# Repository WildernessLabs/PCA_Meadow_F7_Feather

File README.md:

# PCA_Meadow_F7_Micro
PCA (Printed Circuit Assembly) design for the F7 Micro development board.

## Drawings
* [Schematic](https://github.com/WildernessLabs/PCA_Meadow_F7_Micro/blob/main/Assembly/PCA_Meadow_F7_Micro_SCH_V2c.pdf)
* [Top Assembly](https://github.com/WildernessLabs/PCA_Meadow_F7_Micro/blob/main/Assembly/PCA_Meadow_F7_MicroV2c.pdf)
* [BOM](https://github.com/WildernessLabs/PCA_Meadow_F7_Micro/blob/main/Assembly/PCA_Meadow_F7_Micro_bom_V2c.xlsx)

## Pin Out
### Left Header

| F7 Pin Name | STM Pin Function Name | Alt Functions | Additional Functions |
|-------------|-------------|-------------------------|-----------|
| `A00` | `PA4` | SPI1_NSS/I2S1_WS, SPI3_NSS/I2S3_WS, USART2_CK, SPI6_NSS, OTG_HS_SOF, DCMI_HSYNC, LCD_VSYNC, EVENTOUT | ADC1_IN4, ADC2_IN4, DAC_OUT1 |
| `A01` | `PA5` | TIM2_CH1/TIM2_ETR, TIM8_CH1N, SPI1_SCK/I2S1_CK, SPI6_SCK, OTG_HS_ULPI_CK, LCD_R4, EVENTOUT | ADC1_IN5, ADC2_IN5, DAC_OUT2 |
| `A02` | `PA3` | TIM2_CH4, TIM5_CH4, TIM9_CH2, USART2_RX, LCD_B2, OTG_HS_ULPI_D0, ETH_MII_COL, LCD_B5, EVENTOUT | ADC1_IN3, ADC2_IN3, ADC3_IN |
| `A03` | `PB0` | TIM1_CH2N, TIM3_CH3, TIM8_CH2N, DFSDM_CKOUT, UART4_CTS, LCD_R3, OTG_HS_ULPI_D1, ETH_MII_RXD2, LCD_G1, EVENTOUT | ADC1_IN8, ADC2_IN8 |
| `A04` | `PB1` | TIM1_CH3N, TIM3_CH4, TIM8_CH3N, DFSDM_DATIN1, LCD_R6, OTG_HS_ULPI_D2, ETH_MII_RXD3, LCD_G0, EVENTOUT | ADC1_IN9, ADC2_IN9 |
| `A05` | `PC0` | DFSDM_CKIN0, DFSDM_DATIN4, SAI2_FS_B, OTG_HS_ULPI_STP, FMC_SDNWE, LCD_R5, EVENTOUT | ADC1_IN10, ADC2_IN10, ADC3_IN10 |
| `SPI3_SCK` | `PC10` | DFSDM_CKIN5, SPI3_SCK/I2S3_CK, USART3_TX, UART4_TX, QUADSPI_BK1_IO1, SDMMC1_D2, DCMI_D8, LCD_R2, EVENTOUT |
| `SPI3_COPI` | `PB5` | UART5_RX, TIM3_CH2, I2C1_SMBA, SPI1_MOSI/I2S1_SD, SPI3_MOSI/I2S3_SD, SPI6_MOSI, CAN2_RX, OTG_HS_ULPI_D7, ETH_PPS_OUT, FMC_SDCKE1, DCMI_D10, LCD_G7, EVENTOUT |
| `SPI3_CIPO` | `PC11` | DFSDM_DATIN5, SPI3_MISO, USART3_RX, UART4_RX, QUADSPI_BK2_NCS, SDMMC1_D3, DCMI_D4, EVENTOUT |
| `D00`/`COM4_RX` | `PI9` | UART4_RX, CAN1_RX, FMC_D30, LCD_VSYNC, EVENTOUT |
| `D01`/`COM4_TX` | `PH13` | TIM8_CH1N, UART4_TX, CAN1_TX, FMC_D21, LCD_G2, EVENTOUT |
| `D02` | `PH10` | TIM5_CH1, I2C4_SMBA, FMC_D18, DCMI_D1, LCD_R4, EVENTOUT |
| `D03`/`CAN_RX` | `PB8` | I2C4_SCL, TIM4_CH3, TIM10_CH1, I2C1_SCL, DFSDM_CKIN7, UART5_RX, CAN1_RX, SDMMC2_D4, ETH_MII_TXD3, SDMMC1_D4, DCMI_D6, LCD_B6, EVENTOUT |
| `D04`/`CAN_TX` | `PB9` | I2C4_SDA, TIM4_CH4, TIM11_CH1, I2C1_SDA, SPI2_NSS/I2S2_WS, DFSDM_DATIN7, UART5_TX, CAN1_TX, SDMMC2_D5, I2C4_SMBA, SDMMC1_D5, DCMI_D7, LCD_B7, EVENTOUT |

### Right Header

| F7 Pin Name | STM Pin Function Name | Alt Functions | Additional Functions |
|-------------|-------------|-------------------------|-----------|
| `D05` | `PB4` | NJTRST, TIM3_CH1, SPI1_MISO, SPI3_MISO, SPI2_NSS/I2S2_WS, SPI6_MISO, SDMMC2_D3, CAN3_TX, UART7_TX, EVENTOUT |
| `D06`/`I2S2_CK` | `PB13` | I2C2_SMBA, SPI5_SCK, TIM12_CH1, ETH_MII_RXD2, FMC_SDNE1, DCMI_D8, EVENTOUT |
| `D07`/`I2C_SDA` | `PB7` | TIM4_CH2, I2C1_SDA, DFSDM_CKIN5, USART1_RX, I2C4_SDA, FMC_NL, DCMI_VSYNC, EVENTOUT |
| `D08`/`I2C_SCK` | `PB6` | UART5_TX, TIM4_CH1, HDMI_CEC, I2C1_SCL, DFSDM_DATIN5, USART1_TX, CAN2_TX, QUADSPI_BK1_NCS, I2C4_SCL, FMC_SDNE1, DCMI_D5, EVENTOUT |
| `D09`/`I2S2_MCK`/`COM6_TX` | `PC6` | TIM3_CH1, TIM8_CH1, I2S2_MCK, DFSDM_CKIN3, USART6_TX, FMC_NWAIT, SDMMC2_D6, SDMMC1_D6, DCMI_D0, LCD_HSYNC, EVENTOUT |
| `D10`/`COM6_RX` | `PC7` | TIM3_CH2, TIM8_CH2, I2S3_MCK, DFSDM_DATIN3, USART6_RX, FMC_NE1, SDMMC2_D7, SDMMC1_D7, DCMI_D1, LCD_G6, EVENTOUT |
| `D11`/`I2S2_CKIN` | `PC9` | MCO2, TIM3_CH4, TIM8_CH4, I2C3_SDA, I2S_CKIN, UART5_CTS, QUADSPI_BK1_IO0, LCD_G3, SDMMC1_D1, DCMI_D3, LCD_B2, EVENTOUT |
| `D12`/`COM1_TX` | `PB14` | TIM1_CH2N, TIM8_CH2N, USART1_TX, SPI2_MISO, DFSDM_DATIN2, USART3_RTS, UART4_RTS, TIM12_CH1, SDMMC2_D0, OTG_HS_DM, EVENTOUT |
| `D13`/`COM1_RX`/`I2S2_SD` | `PB15` | RTC_REFIN, TIM1_CH3N, TIM8_CH3N, USART1_RX, SPI2_MOSI/I2S2_SD, DFSDM_CKIN2, UART4_CTS, TIM12_CH2, SDMMC2_D1, OTG_HS_DP, EVENTOUT |
| `D14`/`I2S2_WS` | `PB12` | TIM1_BKIN, I2C2_SMBA, SPI2_NSS/I2S2_WS, DFSDM_DATIN1, USART3_CK, UART5_RX, CAN2_RX, OTG_HS_ULPI_D5, ETH_MII_TXD0/ETH_RMII _TXD0, OTG_HS_ID, EVENTOUT |
| `D15` | `PG12` | LPTIM1_IN1, SPI6_MISO, SPDIF_RX1, USART6_RTS, LCD_B4, SDMMC2_D3, FMC_NE4, LCD_B1, EVENTOUT |

## Change Log

### Revision V2.D
* Move to Kicad 6.0.2
* 5V pin is now connected directly to 5V VBUS. Note: If you try to power directly from an external source and connect USB cable you can damage your USB port.
* More schematic clean up
* Change name to F7 Feather

### Revision V2.C1
* Documentaion Changes to Fab Drawing: 
  * do not modify pad sizes without permission from Wilderness Labs
  * fixed errors in stack up and other parts of the notes
* Cleaned up folders to remove all rev B files and zip up rev 2.C files
### Revison V2.C 
* Fixed issue with Batery and VBUS, 
### Revision V2.B
 * Added pogo test points for usb [Schematic and Layout]
 * Changed part number for flash (U2) [Schematic /BOM ]
 * Made pads for Buttons 10% smaller in each directions [Layout]
 * Matched the Trace width of the Quad SPI to the Flash chip [Layout]
 * LDO changed to have lower drop out voltage. 3.3V wasn't regulated when using the batter [Schematic/BOM, and Layout]
 * New LDO has an Enable input so removed the power FET that turned on/off the power to the LDO. Drop out now 0.35V should work 20 - 3.6V. anything above 7V will probably break the LDO under continuous load.
 * Changed pinout of the main headers [Schematic and Layout]

### Revision V2.A
 * Added castelations for JTAG and ESP32 UART
 * Upgrade flash to 512Mega Bit part
 * Changed the USB power switch to remove the discharge circuit.

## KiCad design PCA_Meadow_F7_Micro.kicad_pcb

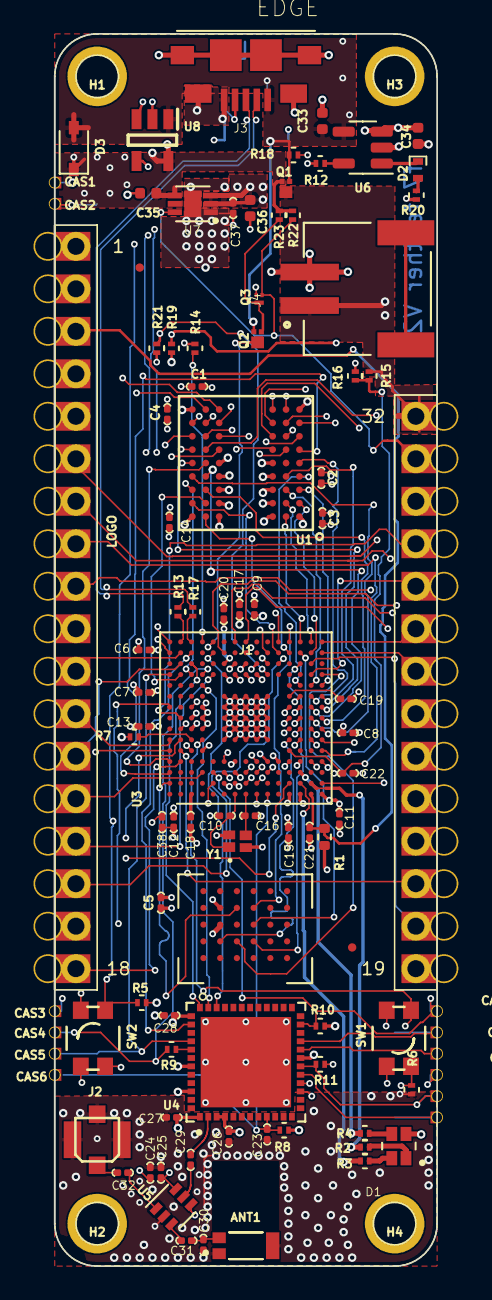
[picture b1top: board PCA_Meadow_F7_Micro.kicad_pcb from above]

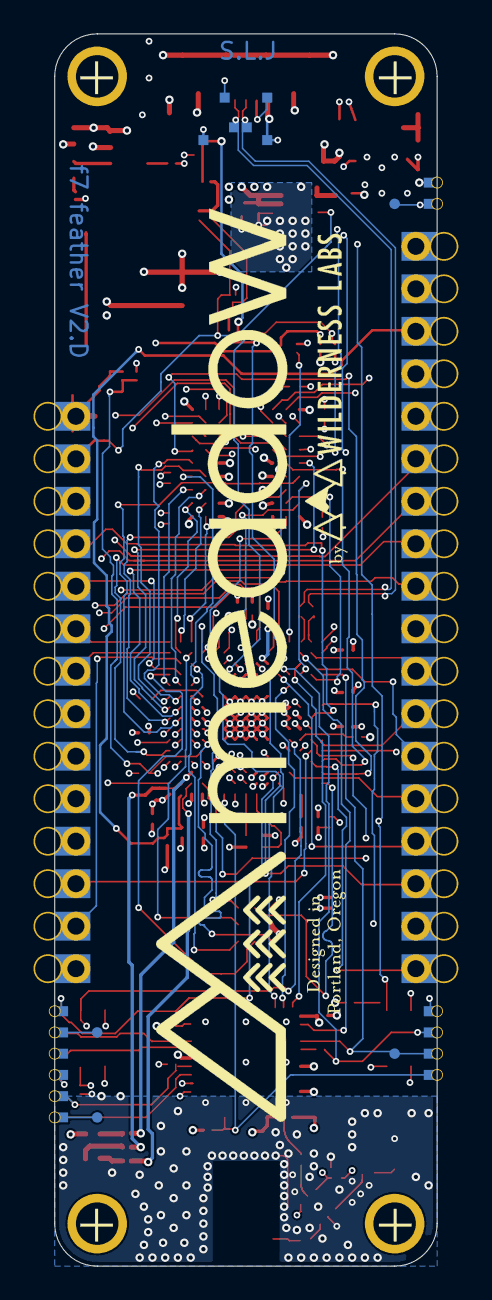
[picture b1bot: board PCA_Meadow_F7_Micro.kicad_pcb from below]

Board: 6 copper layers, 22.9 x 73.7 mm, 110 parts (10 on the bottom side), 128 nets.

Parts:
ANT1: W3008C; ANTENNA_W3008C
C1, C6, C7, C8, C9, C11, C12, C13, C14, C15, C17, C18, C21: C_0201_0.47UF_6.3V_X5R; C_0201
C2, C3, C4, C5, C22, C23, C24, C25, C37, C38: C_0201_0.1UF_10V_X5R; C_0201
C10, C16: C_0201_8pF_50V_C0G; C_0201
C19, C20: C_0201_2.2UF_10V_X5R; C_0201
C26, C27, C28: C_0201_4.7UF_6.3V_X5R; C_0201
C29, C31, C32: C_0201_100PF_50V_C0G; C_0201
C30: C_0201_1.8pF_50V_C0G; C_0201
C33, C34: C_0402_4.7UF_10V_X5R_10%; C_0402_1005Metric
C35, C36: C_0402_10UF_10V_X5R; C_0402_1005Metric
CAS1, CAS2, CAS3, CAS4, CAS5, CAS6, CAS7, CAS8, CAS9, CAS10, CAS11, CAS12: CAST_0.6X0.8MM; CAST_SQ_0.6X0.8MM
D1: LTST-C19HE1WT; LED_LTST-C19HE1WT
D2: LED_O_QBLP595-O; LED_0402
D3: BAT60A; D_SOD-323
H1, H2, H3, H4: MTGP356H254
J1: MEADOWF7MICRO_WITH_CAST_OUTLINE; MeadowF7Micro_w_cast
J2: A-1JB; AMPHENOL_A-1JB
J3: USB_OTG_ZX62-AB-5PA(31); HIROSE_ZX62-AB-5PA
J4: S2B-PH-SM4-TB(LF)(SN); JST_S2B-PH-SM4-TB(LF)(SN)
LOGO: LOGO; silkv2d
Q1, Q2: P-CH_SSM3J46CTB; CST3b_TOS
Q3: N-CH_RV1C002UNT2CL; RV1C002UNT2CL
R1: R_0_1%_0402; R_0402_1005Metric
R2: R_620_1%_0201; R_0201
R3, R4: R_300_1%_0201; R_0201
R5, R6, R7, R8, R11, R18, R21, R22, R23: R_10K_1%_0201; R_0201
R9: R_499_1%_0201; R_0201
R10, R19: R_20K_1%_0201; R_0201
R12: R_4K7_1%_0201; R_0201
R13, R14, R17: R_0_1%_0201; R_0201
R15, R16: R_499K_1%_0201; R_0201
R20: R_1K_1%_0201; R_0201
SW1, SW2: SW_434153017835; WURTH_434153017835
TP1, TP2, TP3, TP4: TestPoint_SMT_25mil; PAD_RD_0.63
TP5, TP6, TP7, TP8, TP9, TP10: PAD_0.6X0.6MM; PAD_SQ_0.6X0.6MM
U1: IS42S16160J-7BLI; TFBGA-54
U2: W25Q512JVBIQ; BGA24C100P6X4_800X600X120N
U3: STM32F777IIKx; UFBGA-201_10x10mm_Layout15x15_P0.65mm
U4: ESP32-PICO-D4; PQFN50P700X700X104-49N
U5: SKYA21001; SOT-363_SC-70-6
U6: MCP73831T-2A; SOT-23-5
U7: LDL212PV33R; SON50P200X200X80-7N
U8: TPS2065CDBVR-2; SOT95P280X145-5N
Y1: ABM12W-25.0000MHZ-6-B1U-T3; XTAL_ABM12W-24.0000MHZ-6-B1U-T3

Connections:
+3V3: C1.1, C2.1, C3.1, C4.1, C5.1, C6.1, C7.1, C8.1, C9.1, C11.1, C12.1, C13.1, C14.1, C15.1, C17.1, C26.1, C27.1, C28.1, C36.1, C37.1, D1.4, J1.2 (+3V3), R1.1, R5.1, R7.1, R8.1, R10.1, R19.1, SW1.1, SW1.3, U1.A7 (VDDQ), U1.A9 (VDD), U1.B3 (VDDQ), U1.C7 (VDDQ), U1.D3 (VDDQ), U1.E7 (VDD), U1.J9 (VDD), U2.B4 (VCC), U3.C5 (VDD), U3.C7 (VDD), U3.C8 (VDDSDMMC), U3.C9 (VDD), U3.F3 (VDD), U3.G3 (VDD), U3.G13 (VDD), U3.H13 (VDDUSB), U3.J12 (VDD), U3.J13 (VDD), U3.K4 (VDD), U3.N8 (VDD), U3.N9 (VDD), U3.N10 (VDD), U3.R1 (VDDA), U4.1 (VDDA), U4.3 (VDDA3P3), U4.4 (VDDA3P3), U4.19 (VDD3P3_RTC), U4.37 (VDD3P3_CPU), U4.43 (VDDA), U4.46 (VDDA), U7.2 (SENSE), U7.3 (VOUT)
+5V: C35.1, D3.1 (K), Q1.2 (SOURCE), R22.1, R23.1, U7.4 (VIN), U8.5 (IN)
+VBAT: C34.1, J1.32 (+VBAT), J4.1, Q1.3 (DRAIN), R15.1, U6.3 (VBAT)
/+5V_VBUS: C33.1, D3.2 (A), J1.30 (+5V), J3.1 (VBUS), Q1.1 (GATE), Q2.2 (SOURCE), R18.1, R20.1, TP9.1, U6.4 (VDD), U8.1 (OUT)
/BOOT0: R6.1, SW1.2, SW1.4, U3.D6 (BOOT0)
/EN_3V3: J1.31 (EN_+3V3), Q3.1 (G), R22.2, U7.6 (EN)
/ESP32/CHIP_ANT: C31.2, U5.3 (J2)
/ESP32/EXT_ANT: C32.1, U5.1 (J3)
/ESP32/GPIO26: C25.1, U4.15 (IO26), U5.6 (V2)
/ESP32/GPIO27: C24.1, U4.16 (IO27), U5.4 (V1)
/ESP32/LNA_50OHM: C29.2, U4.2 (LNA_IN)
/ESP32_BOOT_L_PI10: CAS12.1, R10.2, U3.E3 (PI10), U4.23 (IO0)
/ESP32_MTCK: CAS10.1, U4.20 (IO13)
/ESP32_MTDI: CAS8.1, R11.1, U4.18 (IO12)
/ESP32_MTDO: CAS11.1, TP2.1, U4.21 (IO15)
/ESP32_MTMS: CAS7.1, TP1.1, U4.17 (IO14)
/ESP32_RESET_L_PF7: C23.1, CAS6.1, R8.2, U3.K1 (PF7), U4.9 (EN)
/ESP32_RX_UART5_TX: CAS5.1, TP3.1, U3.A12 (PC12), U4.40 (U0RXD)
/ESP32_SPI2_CS: U3.E14 (PI0), U4.34 (IO5)
/ESP32_SPI2_MISO: U3.C14 (PI2), U4.38 (IO19)
/ESP32_SPI2_MOSI: U3.C13 (PI3), U4.36 (IO23)
/ESP32_TX_UART5_RX: CAS4.1, R9.1, U3.D12 (PD2)
/ESP_32_SPI2_CLK: U3.D11 (PD3), U4.35 (IO18)
/LIPO_BAT_MEAS: C22.1, R15.2, R16.1, U3.M5 (PC3)
/PA0: R4.2, U3.N3 (PA0)
/PA1: R3.2, U3.N2 (PA1)
/PA2: R2.2, U3.P2 (PA2)
/PA3_ADC1_IN3: J1.7 (A2), U3.R2 (PA3)
/PA4_DAC_OUT1: J1.5 (A0), U3.N4 (PA4)
/PA5_DAC_OUT2: J1.6 (A1), U3.P4 (PA5)
/PA9_VBUS: Q2.3 (DRAIN), U3.E15 (PA9)
/PA10_USB_ID: R14.1, U3.D15 (PA10)
/PA13_SWDIO: CAS1.1, U3.A15 (PA13)
/PA14_SWCLK: CAS2.1, TP4.1, U3.A14
/PB0_ADC1_IN8: J1.8 (A3), U3.R5 (PB0)
/PB1_ADC1_IN9: J1.9 (A4), U3.R4 (PB1)
/PB4: J1.19 (D05/COM7_TX), U3.A9 (PB4)
/PB5_SPI3_COPI: J1.12 (COPI), U3.A6 (PB5)
/PB6_I2C1_SCL: J1.22 (D08/I2C_SCK), U3.B6
/PB7_I2C1_SDA: J1.21 (D07/I2C_SDA), U3.B5 (PB7)
/PB8_CAN1_RX: J1.17 (D03/CAN_RX), U3.A5 (PB8)
/PB9_CAN1_TX: J1.18 (D04/CAN_TX), U3.B4 (PB9)
/PB12: J1.28 (D14), U3.P12 (PB12)
/PB13: J1.20 (D06/COM7_RX), U3.P13 (PB13)
/PB14_USART1_TX: J1.26 (D12/COM1_TX), U3.R14 (PB14)
/PB15_USART1_RX: J1.27 (D13/COM1_RX), U3.R15 (PB15)
/PC0_ADC1_IN10: J1.10 (A5), U3.M2 (PC0)
/PC2_OTG_FS_OC: R19.2, U3.M4 (PC2), U8.3 (~FLT)
/PC6_TIM3CH1: J1.23 (D09/COM6_TX), U3.H15 (PC6)
/PC7_TIM3CH2: J1.24 (D10/COM6_RX), U3.G15 (PC7)
/PC9_TIM8CH4: J1.25 (D11), U3.F14 (PC9)
/PC10_SPI3_SCK: J1.11 (SCK), U3.B14 (PC10)
/PC11_SPI3_CIPO: J1.13 (CIPO), U3.B13 (PC11)
/PG12: J1.29 (D15), U3.B8 (PG12)
/PH10: J1.16 (D02), U3.L13 (PH10)
/PH12_OTG_FS_PWRON: R21.1, U3.K12 (PH12), U8.4 (EN/~EN)
/PH13_UART4_TX: J1.15 (D01/COM4_TX), U3.E12 (PH13)
/PI9_UART4_RX: J1.14 (D00/COM4_RX), U3.D3 (PI9)
/QUAD_SPI.CS_L: U2.C2 (CS_L), U3.R12 (PB10)
/QUAD_SPI.IO0: U2.D3 (IO0/SI), U3.N14 (PD11)
/QUAD_SPI.IO1: U2.D2 (IO1/SO), U3.N13 (PD12)
/QUAD_SPI.IO2: U2.C4 (IO2/WP_L), U3.A2 (PE2)
/QUAD_SPI.IO3: U2.D4 (IO3/RESET_L), U3.M15 (PD13)
/QUAD_SPI.SCK: U2.B2 (SCK), U3.M6 (PB2)
/RAM.A0: U1.H7 (A0), U3.E2 (PF0)
/RAM.A1: U1.H8 (A1), U3.H3 (PF1)
/RAM.A2: U1.J8 (A2), U3.H2 (PF2)
/RAM.A3: U1.J7 (A3), U3.J2 (PF3)
/RAM.A4: U1.J3 (A4), U3.J3 (PF4)
/RAM.A5: U1.J2 (A5), U3.K3 (PF5)
/RAM.A6: U1.H3 (A6), U3.P6 (PF12)
/RAM.A7: U1.H2 (A7), U3.N6 (PF13)
/RAM.A8: U1.H1 (A8), U3.R7 (PF14)
/RAM.A9: U1.G3 (A9), U3.P7 (PF15)
/RAM.A10: U1.H9 (A10), U3.N7 (PG0)
/RAM.A11: U1.G2 (A11), U3.M7 (PG1)
/RAM.A12: U1.G1 (A12), U3.L15 (PG2)
/RAM.A14: U1.G7 (BA0), U3.K14 (PG4)
/RAM.A15: U1.G8 (BA1), U3.K13 (PG5)
/RAM.CKE_L: U1.F3 (CKE), U3.F4 (PH2)
/RAM.CLK: U1.F2 (CLK), U3.H14 (PG8)
/RAM.CS_L: U1.G9 (CS_L), U3.G4 (PH3)
/RAM.DQMH: U1.F1 (DQMH), U3.A3 (PE1)
/RAM.DQML: U1.E8 (DQML), U3.A4 (PE0)
/RAM.RAS_L: U1.F8 (RAS_L), U3.R6 (PF11)
/RAM.WE_L: U1.F9 (WE_L), U3.J4 (PH5)
/RAM_CAS_L: U1.F7 (CAS_L), U3.B7 (PG15)
/RAM_DQ0: U1.A8 (DQ0), U3.M14 (PD14)
/RAM_DQ1: U1.B9 (DQ1), U3.L14 (PD15)
/RAM_DQ2: U1.B8 (DQ2), U3.B12 (PD0)
/RAM_DQ3: U1.C9 (DQ3), U3.C12 (PD1)
/RAM_DQ4: U1.C8 (DQ4), U3.R8 (PE7)
/RAM_DQ5: U1.D9 (DQ5), U3.P8 (PE8)
/RAM_DQ6: U1.D8 (DQ6), U3.P9 (PE9)
/RAM_DQ7: U1.E9 (DQ7), U3.R9 (PE10)
/RAM_DQ8: U1.E1 (DQ8), U3.P10 (PE11)
/RAM_DQ9: U1.D2 (DQ9), U3.R10 (PE12)
/RAM_DQ10: U1.D1 (DQ10), U3.N11 (PE13)
/RAM_DQ11: U1.C2 (DQ11), U3.P11 (PE14)
/RAM_DQ12: U1.C1 (DQ12), U3.R11 (PE15)
/RAM_DQ13: U1.B2 (DQ13), U3.P15 (PD8)
/RAM_DQ14: U1.B1 (DQ14), U3.P14 (PD9)
/RAM_DQ15: U1.A2 (DQ15), U3.N15 (PD10)
/RESET_L: C38.1, J1.1 (RESET_L), R5.2, SW2.1, SW2.3, U3.J1 (NRST)
/STM32F7/OSC_IN_PH0: C10.1, U3.G1 (PH0), Y1.1
/STM32F7/OSC_OUT_PH1: C16.1, U3.H1, Y1.3
/STM32F7/PDR_ON: R7.2, U3.C6 (PDR_ON)
/STM32F7/VCAP1: C19.1, U3.M10 (VCAP_1)
/STM32F7/VCAP2: C20.1, U3.F13 (VCAP_2)
/USB_D_N: R17.1, U3.C15 (PA11)
/USB_D_P: R13.1, U3.B15 (PA12)
/USB_POWER/EN_3V3_L: Q2.1 (GATE), Q3.3 (D), R23.2
/USB_POWER/USB_D_N: J3.2 (D-), R17.2, TP7.1
/USB_POWER/USB_D_P: J3.3 (D+), R13.2, TP6.1
/USB_POWER/USB_ID: J3.4 (ID), R14.2, TP8.1
/VBAT: C18.1, U3.C1 (VBAT)
/VREF: C21.1, J1.3 (AREF), R1.2, U3.P1 (VREF+)
GND: ANT1.G1 (GND), ANT1.G2 (GND), C1.2, C2.2, C3.2, C4.2, C5.2, C6.2, C7.2, C8.2, C9.2, C10.2, C11.2, C12.2, C13.2, C14.2, C15.2, C16.2, C17.2, C18.2, C19.2, C20.2, C21.2, C22.2, C23.2, C24.2, C25.2, C26.2, C27.2, C28.2, C30.2, C33.2, C34.2, C35.2, C36.2, C37.2, C38.2, CAS3.1, CAS9.1, J1.4 (GND), J2.GND1 (GND), J2.GND2 (GND), J2.OPTIONAL_GND (GND), J3.5 (GND), J3.6 (Shield), J4.2, Q3.2 (S), R6.2, R11.2, R12.2, R16.2, R18.2, R21.2, SW2.2, SW2.4, TP5.1, TP10.1, U1.A1 (VSS), U1.A3 (VSSQ), U1.B7 (VSSQ), U1.C3 (VSSQ), U1.D7 (VSSQ), U1.E3 (VSS), U1.J1 (VSS), U2.B3 (VSS), U3.D5 (VSS), U3.D7 (VSS), U3.D8 (VSS), U3.D9 (VSS), U3.F2 (VSS), U3.F6 (VSS), U3.F7 (VSS), U3.F8 (VSS), U3.F9 (VSS), U3.F10 (VSS), U3.F12 (VSS), U3.G2 (VSS), U3.G6 (VSS), U3.G7 (VSS), U3.G8 (VSS), U3.G9 (VSS), U3.G10 (VSS), U3.G12 (VSS), U3.H6 (VSS), U3.H7 (VSS), U3.H8 (VSS), U3.H9 (VSS), U3.H10 (VSS), U3.H12 (VSS), U3.J6 (VSS), U3.J7 (VSS), U3.J8 (VSS), U3.J9 (VSS), U3.J10 (VSS), U3.K6 (VSS), U3.K7 (VSS), U3.K8 (VSS), U3.K9 (VSS), U3.K10 (VSS), U3.L4 (BYPASS_REG), U3.M1 (VSSA), U3.M8 (VSS), U3.M9 (VSS), U3.N1 (VREF-), U4.49 (GND), U5.2 (GND), U6.2 (VSS), U7.1 (GND), U7.7 (GND), U8.2 (GND), Y1.2, Y1.4
unnamed: ANT1.FEED, C30.1, C31.1
unnamed: C29.1, U5.5 (J1)
unnamed: C32.2, J2.SIGNAL
unnamed: D1.1, R2.1
unnamed: D1.2, R3.1
unnamed: D1.3, R4.1
unnamed: D2.1 (A), R20.2
unnamed: D2.2 (K), U6.1 (STAT)
unnamed: R9.2, U4.41 (U0TXD)
unnamed: R12.1, U6.5 (PROG)

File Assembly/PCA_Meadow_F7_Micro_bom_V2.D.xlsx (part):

Component | Quantity Per PCB | References | DNI | PN | MF | PN2 | MF2 | Part | Description | Value | Footprint
1 | 1 | ANT1 |  | W3008C | PulseLarsen Antennas |  |  | W3008C | 2.4GHz Bluetooth Chip RF Antenna 2.4GHz ~ 2.483GHz 1.7dBi Solder Surface Mount | W3008C | ANTENNA_W3008C
2 | 10 | C2 C3 C4 C5 C22 C23 C24 C25 C37 C38 |  | GRM033R61A104KE15D | Murata Electronics North America | CL03A104KP3NNNC | Samsung Electro-Mechanics | C_0201_0.1UF_10V_X5R | 0.1µF ±10% 10V Ceramic Capacitor X5R 0201 (0603 Metric) | C_0201_0.1UF_10V_X5R | C_0201
3 | 13 | C1 C6 C7 C8 C9 C11 C12 C13 C14 C15 C17 C18 C21 |  | GRM033R60J474KE90D | Murata Electronics North America | CL03A474KQ3NNNH | Samsung Electro-Mechanics | C_0201_0.47UF_6.3V_X5R | 0.47µF ±10% 6.3V Ceramic Capacitor X5R 0201 (0603 Metric) | C_0201_0.47UF_6.3V_X5R | C_0201
4 | 1 | C30 |  | GRM0335C1H1R8CA01D | Murata Electronics North America | CC0201BRNPO9BN1R8 | Yageo | C_0201_1.8pF_50V_C0G | 1.8pF ±0.25pF 50V Ceramic Capacitor C0G, NP0 0201 (0603 Metric) | C_0201_1.8pF_50V_C0G | C_0201
5 | 3 | C29 C31 C32 |  | GRM0335C1H101JA01D | Murata Electronics North America | VJ0201A101JXACW1BC-ND | Vishay | C_0201_100PF_50V_C0G | 100pF ±5% 50V Ceramic Capacitor C0G, NP0 0201 (0603 Metric) | C_0201_100PF_50V_C0G | C_0201
6 | 2 | C19 C20 |  | GRM033R61A225KE47D | Murata Electronics North America | CL03A225MP3CRNC | Samsung Electro-Mechanics | C_0201_2.2UF_10V_X5R | 2.2µF ±10% 10V Ceramic Capacitor X5R 0201 (0603 Metric) | C_0201_2.2UF_10V_X5R | C_0201
7 | 3 | C26 C27 C28 |  | GRM035R60J475ME15D | Murata Electronics North America |  |  | C_0201_4.7UF_6.3V_X5R | 4.7µF ±20% 6.3V Ceramic Capacitor X5R 0201 (0603 Metric) | C_0201_4.7UF_6.3V_X5R | C_0201
8 | 2 | C10 C16 |  | GRM0335C1H8R0DA01J | Murata Electronics North America | CC0201DRNPO9BN8R0 | Yageo | C_0201_8pF_50V_C0G | 8pF ±0.5pF 50V Ceramic Capacitor C0G, NP0 0201 (0603 Metric) | C_0201_8pF_50V_C0G | C_0201
9 | 2 | C35 C36 |  | CL05A106MP5NUNC | Samsung Electro-Mechanics | CL05A106MP8NUB8 | Samsung Electro-Mechanics | C_0402_10UF_10V_X5R | 10µF ±20% 10V Ceramic Capacitor X5R 0402 (1005 Metric) | C_0402_10UF_10V_X5R | C_0402_1005Metric
10 | 2 | C33 C34 |  | CL05A475KQ5NRNC | Samsung Electro-Mechanics | CC0402KRX5R5BB475 | Yageo | C_0402_4.7UF_10V_X5R_10% | CAP CER 4.7UF 6.3V X5R 0402 | C_0402_4.7UF_10V_X5R_10% | C_0402_1005Metric
11 | 1 | D3 |  | BAT60AE6327HTSA1 | Infineon Technologies |  |  | BAT60A | Diode Schottky 10V 3A (DC) Surface Mount PG-SOD323-2 | BAT60A | D_SOD-323
12 | 1 | D2 |  | QBLP595-O | QT Brightek (QTB) |  |  | LED_O_QBLP595-O | Orange 605nm LED Indication - Discrete 2V 0402 (1005 Metric) | LED_O_QBLP595-O | LED_0402
13 | 1 | D1 |  | LTST-C19HE1WT | Lite-On Inc. |  |  | LTST-C19HE1WT | Red, Green, Blue (RGB) 624nm Red, 525nm Green, 470nm Blue LED Indication - Disc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 | LTST-C19HE1WT | LED_LTST-C19HE1WT
14 | 1 | J2 |  | A-1JB | Amphenol RF Division |  |  | A-1JB | U.FL (UMCC), AMC Connector Jack, Male Pin 50Ohm Surface Mount Solder | A-1JB | AMPHENOL_A-1JB
15 | 1 | J4 |  | S2B-PH-SM4-TB(LF)(SN) | JST |  |  | S2B-PH-SM4-TB(LF)(SN) | Connector Header Surface Mount, Right Angle 2 position 0.059" (1.50mm) | S2B-PH-SM4-TB(LF)(SN) | JST_S2B-PH-SM4-TB(LF)(SN)
16 | 1 | J3 |  | ZX62-AB-5PA(31) | Hirose Electric Co Ltd |  |  | USB_OTG_ZX62-AB-5PA(31) | USB - micro AB USB 2.0 Receptacle Connector 5 Position Surface Mount, Right Ang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 | USB_OTG_ZX62-AB-5PA(31) | HIROSE_ZX62-AB-5PA
17 | 1 | Q3 |  | RV1C002UNT2CL | Rohm Semiconductor |  |  | N-CH_RV1C002UNT2CL | N-Channel 20V 150mA (Ta) 100mW (Ta) Surface Mount VML0806 | N-CH_RV1C002UNT2CL | RV1C002UNT2CL
18 | 2 | Q1 Q2 |  | SSM3J46CTB(TPL3) | Toshiba Semiconductor and Storage |  |  | P-CH_SSM3J46CTB | P-Channel 20V 2A (Ta) Surface Mount CST3B | P-CH_SSM3J46CTB | CST3b_TOS
19 | 3 | R13 R14 R17 |  | RC0201JR-070RL | Yageo |  |  | R_0_1%_0201 | 0 Ohms Jumper 0.05W, 1/20W Chip Resistor 0201 (0603 Metric) Moisture Resistant 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 | R_0_1%_0201 | R_0201
20 | 1 | R1 |  | RMCF0402ZT0R00 | Stackpole Electronics Inc | CRCW04020000Z0ED | Vishay Dale | R_0_1%_0402 | RES 0 OHM JUMPER 1/16W 0402 | R_0_1%_0402 | R_0402_1005Metric
21 | 9 | R5 R6 R7 R8 R11 R18 R21 R22 R23 |  | RC0201FR-0710KL | Yageo |  |  | R_10K_1%_0201 | 10 kOhms ±1% 0.05W, 1/20W Chip Resistor 0201 (0603 Metric) Thick Film | R_10K_1%_0201 | R_0201
22 | 1 | R20 |  | RC0201FR-071KL | Yageo | ERJ-1GNF1001C | Panasonic Electronic Components | R_1K_1%_0201 | 1 kOhms ±1% 0.05W, 1/20W Chip Resistor 0201 (0603 Metric) Thick Film | R_1K_1%_0201 | R_0201
23 | 2 | R10 R19 |  | RC0201FR-0720KL | Yageo |  |  | R_20K_1%_0201 | 20 kOhms ±1% 0.05W, 1/20W Chip Resistor 0201 (0603 Metric) Moisture Resistant T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 | R_20K_1%_0201 | R_0201
24 | 2 | R3 R4 |  | RC0201FR-07300RL | Yageo | ERJ-1GEF3000C | Panasonic Electronic Components | R_300_1%_0201 | 300 Ohms ±1% 0.05W, 1/20W Chip Resistor 0201 (0603 Metric) Thick Film | R_300_1%_0201 | R_0201
25 | 2 | R15 R16 |  | RC0201FR-07499KL | Yageo | ERJ-1GNF4993C | Panasonic Electronic Components | R_499K_1%_0201 | 499 kOhms ±1% 0.05W, 1/20W Chip Resistor 0201 (0603 Metric) Automotive AEC-Q200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 | R_499K_1%_0201 | R_0201
26 | 1 | R9 |  | ERJ-1GNF4990C | Panasonic Electronic Components |  |  | R_499_1%_0201 | 499 Ohms ±1% 0.05W, 1/20W Chip Resistor 0201 (0603 Metric) Automotive AEC-Q200 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 | R_499_1%_0201 | R_0201
27 | 1 | R12 |  | RC0201FR-074K7L | Yageo | CRCW02014K70FKED | Vishay Dale | R_4K7_1%_0201 | 4.7 kOhms ±1% 0.05W, 1/20W Chip Resistor 0201 (0603 Metric) Thick Film | R_4K7_1%_0201 | R_0201
28 | 1 | R2 |  | RC0201FR-07620RL | Yageo | ERJ-1GNF6200C | Panasonic Electronic Components | R_620_1%_0201 | 620 Ohms ±1% 0.05W, 1/20W Chip Resistor 0201 (0603 Metric) Thick Film | R_620_1%_0201 | R_0201
29 | 2 | SW1 SW2 |  | 434153017835 | Würth Elektronik |  |  | SW_434153017835 | SWITCH TACTILE SPST-NO 0.05A 12V | SW_434153017835 | WURTH_434153017835
30 | 1 | U4 |  | ESP32-PICO-D4 | Espressif Systems |  |  | ESP32-PICO-D4 | Bluetooth, WiFi 802.11b/g/n, Bluetooth v4.2 + EDR, Class 1, 2 and 3 Transceiver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 | ESP32-PICO-D4 | PQFN50P700X700X104-49N
31 | 1 | U1 |  | IS42S16160J-7BLI | ISSI, Integrated Silicon Solution Inc |  |  | IS42S16160J-7BLI | SDRAM Memory IC 256Mb (16M x 16) Parallel 143MHz 5.4ns 54-TFBGA (8x8) | IS42S16160J-7BLI | TFBGA-54
32 | 1 | U7 |  | LDL212PV33R | STMicroelectronics |  |  | LDL212PV33R | Linear Voltage Regulator IC Positive Fixed Output 1.2A 6-DFN (2x2) | LDL212PV33R | SON50P200X200X80-7N
33 | 1 | U6 |  | MCP73831T-2ACI/OT | Microchip Technology |  |  | MCP73831T-2A | Single cell, Li-Ion/Li-Po charge management controller, 4.20V, Open-Drain Statu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 | MCP73831T-2A | SOT-23-5
34 | 1 | U5 |  | SKYA21001 | Skyworks Solutions Inc. |  |  | SKYA21001 | RF Switch IC Bluetooth, WLAN SPDT 3GHz 50Ohm SC-70-6 | SKYA21001 | SOT-363_SC-70-6
35 | 1 | U3 |  | STM32F777IIK6 | STMicroelectronics |  |  | STM32F777IIKx | ARM Cortex-M7 MCU, 2048KB flash, 384KB RAM, 216MHz, 1.7-3.6V, 140 GPIO, UFBGA-1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 | STM32F777IIKx | UFBGA-201_10x10mm_Layout15x15_P0.65mm
36 | 1 | U8 |  | TPS2065CDBVR-2 | Texas Instruments |  |  | TPS2065CDBVR-2 | Power Switch ICs - Power Distribution Sgl Ch Current-Ltd USB Pwr Disti Switch | TPS2065CDBVR-2 | SOT95P280X145-5N
37 | 1 | U2 |  | W25Q512JVBIQ | Winbond Electronics | W25Q512JVBIM | Winbond Electronics | W25Q512JVBIQ | FLASH - NOR Memory IC 512Mb (32M x 8) SPI - Quad I/O, QPI 133MHz 24-BGA (6x8) D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 | W25Q512JVBIQ | BGA24C100P6X4_800X600X120N
38 | 1 | Y1 |  | ABM12W-25.0000MHZ-6-B1U-T3 | Abracon LLC |  |  | ABM12W-25.0000MHZ-6-B1U-T3 | 25MHz ±10ppm Crystal 6pF 150 Ohms 4-SMD, No Lead | ABM12W-25.0000MHZ-6-B1U-T3 | XTAL_ABM12W-24.0000MHZ-6-B1U-T3
Component Groups: | 43
Component Count: | 109
Fitted Components: | 109
Number of PCBs: | 1
Total components: | 109
Schematic Version: | V2.D
Schematic Date: | 2022-03-26
PCB Variant: | [u'default']
BoM Date: | 4/9/2022 2:09:40 PM
Schematic Source: | PCA_Meadow_F7_Micro.kicad_sch
KiCad Version: | Eeschema (6.0.1-133-gaa5b6c70a7)
Do not install Parts
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
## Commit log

2020-07-12 Added Design files to folder.
2021-01-13 Finished USB/Power schematic sheet
2021-01-18 Added buttons and headers
2021-01-20 Swizzled pins and added LED
    Also put things back on grid.
2021-01-23 placement complete
2021-01-23 added pdf and one cap
2021-01-24 v2 work
2021-01-28 FAn out mostly done
2021-01-29 getting closer
2021-01-31 traces routed clean up to begin
2021-02-01 added pogo test points and step files
2021-02-02 Gerbers done
2021-02-05 Added BOM and updated gerbers to fix errors
2021-02-11 made requested changes
2021-02-12 added gerbers
2021-03-04 Added the gencad to the assembly zip
2021-03-27 fixing ds store thing
2021-03-27 Added the pinout
2021-03-27 Re-ordered pinout and fixed small mistake
2021-04-04 updated pinout to change D05,D06,D15
2021-04-18 Made pinnout changes, added pads for USB and moved to version 2b
2021-04-18 added pdf sch for V2B
2021-04-20 garbage file
2021-04-25 Routed new changes, new LDO, new silk
2021-04-25 Added old drawings zip folder
2021-04-29 Gerbers and Most drawings added for V2B, still needs BOM update
2021-04-29 added the files missing from last commit
2021-04-29 changed fab drawing to Matte Black
2021-04-29 changed fab drawing to Matte Black again
2021-05-02 Added BOM, should be ready for tag and release rev 2B
2021-05-02 update change log in readme
2021-05-02 saved silk changes to PCB
2021-05-06 Made changes requested by RUSH, once we get to assembly i should have a release
2021-05-14 added panelized gerbers
2021-06-06 Fixed BOM, this is REVB, there will be a REVC
2021-06-06 v2C, tied VBUS to Q1 gate to fix issue
2021-06-13 Added some additional pinout info, including free pins.
2021-06-13 fixup table
2021-06-13 Added some more notes.
2021-06-13 cleanup
2021-06-18 Added Gerbers for Rev v2c
2021-06-18 didn't save pcb file
2021-06-22 got rid of old stuff
2021-07-06 added notes on pins
2021-12-12 checking in missing rev C files before adding notes to FABdrawing
2021-12-12 Made Version 2.C.1. This updated the fab drawing and cleaned up some of the files in the repo. Every thing is now V2.C or V2.C.1
2021-12-14 removing zips
2022-01-05 updated `D06` to have correct functions for PB13
2022-02-26 Add PDF schematic back to project
2022-02-26 Added schematic so it will open from readme link
2022-03-27 Converted to Kicad 6.0, cleaned up schematic added Cap to reset line, changed net to 5V pin
2022-03-27 Added pdf schematic, 3D models for parts
2022-04-09 Updated PCB to fix all notes from the digi source, generated gerbers, drawings, pick and place, 3D files and BOM
2022-04-09 Remove backup
2023-03-07 Added 3x2 panel gerbers
2026-03-09 add latest pick and place

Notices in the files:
parts and their libraries:
Copyright 2016 Accelerated Designs. All rights reserved.
